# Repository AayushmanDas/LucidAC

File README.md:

# LucidAC: Smart Universal AC Controller & IR Protocol Sniffer

An open-source, handheld, state-machine-driven universal air conditioner remote and IR protocol analyzer built on the ESP32-C3. Designed for multi-vendor AC control with an intuitive rotary UI, live feedback, and a transparent aesthetic enclosure.

---

## Features

- **State-Driven AC Control:** Implements full multi-byte payload serialization across major manufacturers (Daikin, Carrier, Midea, etc.) rather than simple stateless toggles.
- **Physical Rotary Interface:** Smooth navigation and mode scrubbing via an EC11 rotary encoder paired with a 0.96" SSD1306 I2C OLED display.
- **Live IR Learning & Sniffing:** Integrated TSOP1838 receiver enables on-the-fly packet sniffing and timing inspection without an external logic analyzer.
- **Efficient Power Architecture:** 1S LiPo powered with onboard TP4056 USB-C charging (tuned to ~440mA via custom R_PROG), regulated by an ultra-low-dropout ME6211 3.3V LDO.
- **Light Sleep Wake Engine:** Instantaneous sub-millisecond wakeup on encoder movement and push-button interrupts while conserving battery life.
- **Exposed Aesthetic Enclosure:** Custom 3D-printed chassis with a slide-in acrylic window designed to showcase the PCB layout and passives.

---

## Hardware Architecture

| Subsystem | Component | Notes |
| :--- | :--- | :--- |
| **MCU** | ESP32-C3 SuperMini | Socketed via berg headers for safe, isolated flashing |
| **Display** | 0.96" I2C OLED (SSD1306) | Controlled via `U8g2` with power-save sleep toggling |
| **Input** | EC11 Rotary Encoder + Tactile Switch | Interrupt-driven navigation and wake triggers |
| **Optical TX** | 940nm High-Power IR LED | Driven via switching transistor stage |
| **Optical RX** | TSOP1838 (38kHz) | Demodulated carrier sensing for signal reverse-engineering |
| **Power Management** | TP4056 + DW01A / FS8205A | R_PROG = 2.7kΩ (~440mA CC charge rate) |
| **Rail LDO** | ME6211A33M3G (SOT-23-5) | 500mA rating, low dropout, stabilized with 10µF MLCCs |
| **Audio Feedback** | 3.3V Active Buzzer | Short audible confirmation on transmit and menu clicks |

### Decoupling Strategy
The 3.3V power rail uses a multi-tier decoupling scheme:
- **10µF MLCCs:** Fast loop stability directly at the ME6211 input/output pins.
- **100nF Ceramic:** High-frequency RF and digital switching transient suppression near the MCU.
- **100µF Electrolytic:** Bulk reservoir dampening dynamic load steps from the OLED panel and buzzer bursts.

---

## Pinout Mapping

| Function | ESP32-C3 GPIO | Description |
| :--- | :--- | :--- |
| **I2C SDA** | GPIO 8 | OLED Display Data |
| **I2C SCL** | GPIO 9 | OLED Display Clock |
| **Encoder A (CLK)** | GPIO 4 | Interrupt-driven quadrature input |
| **Encoder B (DT)** | GPIO 5 | Quadrature direction sensing |
| **Encoder SW** | GPIO 3 | Primary selection click |
| **Aux Tactile Switch** | GPIO 2 | Secondary trigger / quick action |
| **IR Transmitter** | GPIO 1 | PWM carrier / protocol modulation |
| **IR Receiver** | GPIO 0 | TSOP1838 demodulated input |
| **Buzzer** | GPIO 10 | Active piezo drive |

---

## Firmware Setup

The firmware is developed using **PlatformIO**.

1. Clone this repository:
   ```bash
   git clone [https://github.com/AayushmanDas/LucidAC.git](https://github.com/AayushmanDas/LucidAC.git)
   cd LucidAC/firmware
   ```
2. Open the `firmware/` directory inside VS Code with the PlatformIO extension installed.
3. Build the project:
   ```bash
   pio run
   ```
4. **Flashing Note:** To prevent back-feeding the carrier board's ME6211 regulator, disconnect the SuperMini from its socket headers or power the board normally before plugging in the USB cable.
5. Upload and open the serial monitor:
   ```bash
   pio run -t upload -t monitor
   ```

---

## Mechanical & 3D Printing

- **Enclosure:** Printable without internal supports on standard FDM printers (PLA or PETG, recommended ≥ 4 perimeter walls, 20% infill).
- **Assembly:** Slide the acrylic faceplate into the top guide rails after securing the PCB.

---

## Bill of Materials (BOM)

A complete CSV list of components, footprint packages, and reference designators can be found in [`hardware/BOM.csv`](hardware/BOM.csv).

---

## License

- [MIT License](LICENSE)

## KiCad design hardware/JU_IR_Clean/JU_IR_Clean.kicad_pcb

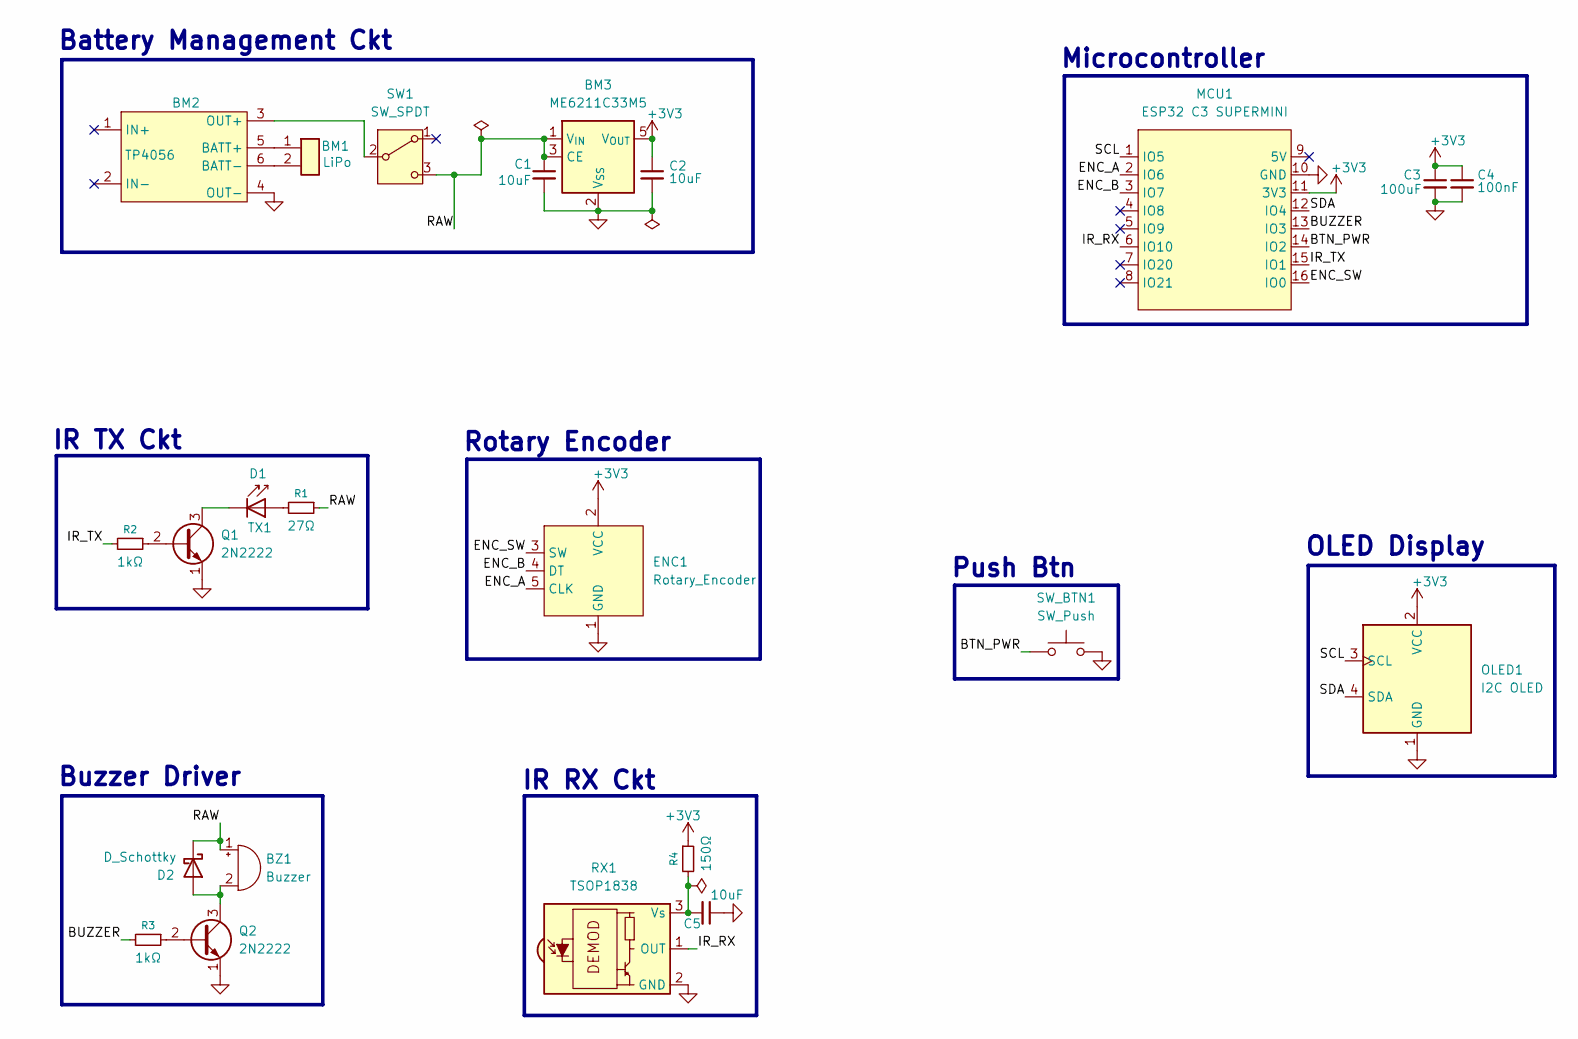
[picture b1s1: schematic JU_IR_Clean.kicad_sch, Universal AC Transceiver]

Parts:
BM1: LiPo; Molex_PicoBlade_53398-0271_1x02-1MP_P1.25mm_Vertical
BM2: TP4056
BM3: ME6211C33M5; SOT-23-5
BZ1: Buzzer; Buzzer_12x9.5RM7.6
C1, C2, C5: 10uF; C_1206_3216Metric_Pad1.33x1.80mm_HandSolder
C3: 100uF; CP_Radial_D6.3mm_P2.50mm
C4: 100nF; C_Disc_D5.0mm_W2.5mm_P2.50mm
D1: TX1; LED_D5.0mm_IRGrey
D2: D_Schottky; D_DO-201AD_P15.24mm_Horizontal
ENC1: Rotary_Encoder; HW-040_Rotary_Encoder
MCU1: ESP32 C3 SUPERMINI; ESP32_C3_SuperMini
OLED1: I2C OLED; OLED_0.96
Q1, Q2: 2N2222; TO-92_Inline
R1: 27Ω; R_Axial_DIN0207_L6.3mm_D2.5mm_P10.16mm_Horizontal
R2, R3: 1kΩ; R_Axial_DIN0207_L6.3mm_D2.5mm_P10.16mm_Horizontal
R4: 150Ω; R_Axial_DIN0207_L6.3mm_D2.5mm_P10.16mm_Horizontal
RX1: TSOP1838; Vishay_MINICAST-3Pin
SW1: SW_SPDT; SolderWire-0.75sqmm_1x03_P4.8mm_D1.25mm_OD2.3mm
SW_BTN1: SW_Push; SW_PUSH_6mm

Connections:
+3V3: BM3.5 (V_{OUT}), C2.1, C3.1, C4.1, ENC1.2 (VCC), MCU1.11 (3V3), OLED1.2 (VCC), R4.1
/BTN_PWR: MCU1.14 (IO2), SW_BTN1.1
/BUZZER: MCU1.13 (IO3), R3.2
/ENC_A: ENC1.5 (CLK), MCU1.2 (IO6)
/ENC_B: ENC1.4 (DT), MCU1.3 (IO7)
/ENC_SW: ENC1.3 (SW), MCU1.16 (IO0)
/IR_RX: MCU1.6 (IO10), RX1.1 (OUT)
/IR_TX: MCU1.15 (IO1), R2.2
/RAW: BM3.1 (V_{IN}), BM3.3 (CE), BZ1.1 (+), C1.1, D2.1 (K), R1.1, SW1.3 (C)
/SCL: MCU1.1 (IO5), OLED1.3 (SCL)
/SDA: MCU1.12 (IO4), OLED1.4 (SDA)
GND: BM2.4 (OUT-), BM3.2 (V_{SS}), C1.2, C2.2, C3.2, C4.2, C5.1, ENC1.1 (GND), MCU1.10 (GND), OLED1.1 (GND), Q1.1 (E), Q2.1 (E), RX1.2 (GND), SW_BTN1.2
unnamed: BM1.1 (+), BM2.5 (BATT+)
unnamed: BM1.2 (-), BM2.6 (BATT-)
unnamed: BM2.3 (OUT+), SW1.2 (B)
unnamed: BZ1.2 (-), D2.2 (A), Q2.3 (C)
unnamed: D1.2 (A), R1.2
unnamed: D1.1 (K), Q1.3 (C)
unnamed: Q1.2 (B), R2.1
unnamed: Q2.2 (B), R3.1
unnamed: C5.2, R4.2, RX1.3 (Vs)

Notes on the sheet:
Battery Management Ckt
Push Btn
OLED Display
Microcontroller
Buzzer Driver
IR RX Ckt
IR TX Ckt
Rotary Encoder

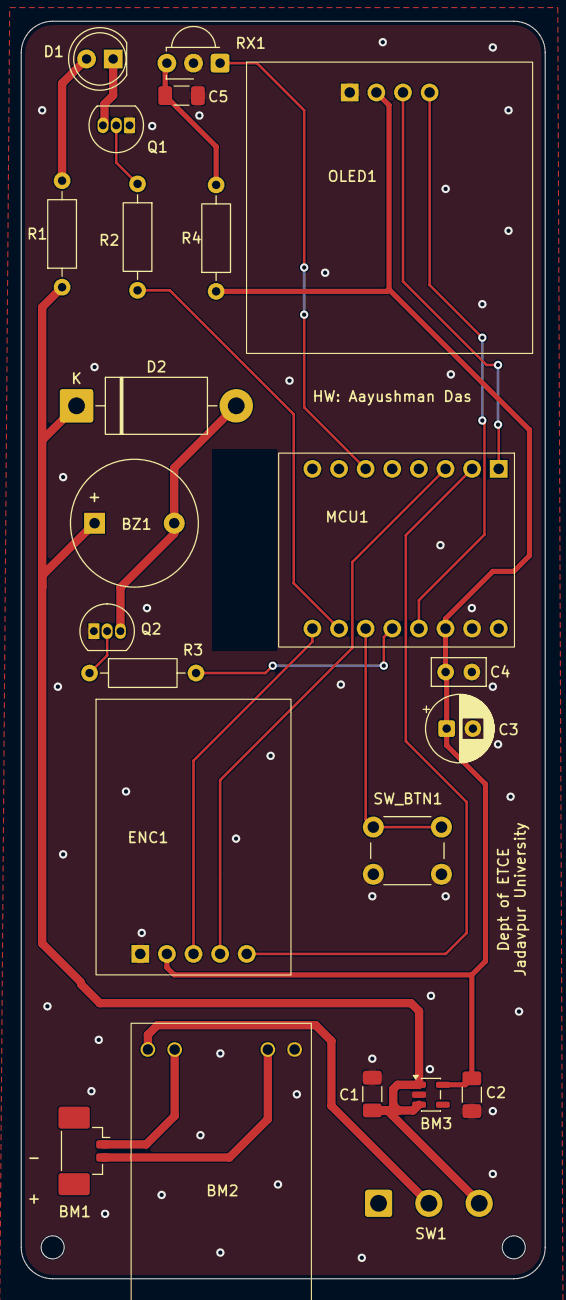
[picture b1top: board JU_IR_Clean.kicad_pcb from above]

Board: 2 copper layers, 50.0 x 120.0 mm, 23 parts (0 on the bottom side), 21 nets.

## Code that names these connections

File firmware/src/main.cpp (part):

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// =================================================================
#define PIN_I2C_SDA     4
#define PIN_I2C_SCL     5
#define PIN_ENC_A       6
#define PIN_ENC_B       7
#define PIN_ENC_SW      0
#define PIN_BTN_PWR     2
#define PIN_BUZZER      3
#define PIN_IR_TX       1
#define PIN_IR_RX       10

// =================================================================
// SYSTEM CONSTANTS & STRUCTURES
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U8G2_SSD1306_128X64_NONAME_F_HW_I2C u8g2(U8G2_R0, U8X8_PIN_NONE);
Preferences prefs;

IRsend irsend(PIN_IR_TX);
IRrecv irrecv(PIN_IR_RX, RAW_BUFFER_CAPACITY, 120, true); // 120 ms gap timeout
decode_results irResults;

// Specific AC Protocol Handlers
IRDaikinESP     irDaikin(PIN_IR_TX);
IRLgAc          irLG(PIN_IR_TX);
IRGreeAC        irVoltas(PIN_IR_TX);   // Voltas via Gree OEM protocol
IRMideaAC       irMidea(PIN_IR_TX);    // Carrier India = Midea OEM (48-bit)
IRHitachiAc     irHitachi(PIN_IR_TX);
IRMitsubishiAC  irMitsubishi(PIN_IR_TX);

// Operational States
AppState currentState = STATE_CONTROL_ROOM;
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// AUDIO FEEDBACK SUBSYSTEM
// =================================================================
void buzzerTrigger(uint16_t durationMs, bool doubleBeep) {
    digitalWrite(PIN_BUZZER, HIGH);
    buzzerStartTime = millis();
    buzzerDuration = durationMs;
    buzzerDoubleBeepPending = doubleBeep;
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    }

    if (buzzerDuration > 0 && (millis() - buzzerStartTime >= buzzerDuration)) {
        digitalWrite(PIN_BUZZER, LOW);
        buzzerDuration = 0;

        if (buzzerDoubleBeepPending) {
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    if (settingsDirty) saveSettings();

    u8g2.setPowerSave(1);
    digitalWrite(PIN_BUZZER, LOW);

    gpio_wakeup_enable((gpio_num_t)PIN_ENC_SW,  GPIO_INTR_LOW_LEVEL);
    gpio_wakeup_enable((gpio_num_t)PIN_BTN_PWR, GPIO_INTR_LOW_LEVEL);
    esp_sleep_enable_gpio_wakeup();

    esp_light_sleep_start();

    esp_sleep_disable_wakeup_source(ESP_SLEEP_WAKEUP_GPIO);
    gpio_wakeup_disable((gpio_num_t)PIN_ENC_SW);
    gpio_wakeup_disable((gpio_num_t)PIN_BTN_PWR);
    u8g2.setPowerSave(0);

    encSwIgnore  = true;
    pwrBtnIgnore = true;

    oldEncoderState = (digitalRead(PIN_ENC_A) << 1) | digitalRead(PIN_ENC_B);
    positionDelta = 0;

    lastActivityTime = millis();
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    Serial.begin(115200);
    delay(500);

    pinMode(PIN_ENC_A,   INPUT_PULLUP);
    pinMode(PIN_ENC_B,   INPUT_PULLUP);
    pinMode(PIN_ENC_SW,  INPUT_PULLUP);
    pinMode(PIN_BTN_PWR, INPUT_PULLUP);
    pinMode(PIN_BUZZER,  OUTPUT);
    digitalWrite(PIN_BUZZER, LOW);

    oldEncoderState = (digitalRead(PIN_ENC_A) << 1) | digitalRead(PIN_ENC_B);

    Wire.begin(PIN_I2C_SDA, PIN_I2C_SCL);
    u8g2.setBusClock(400000);
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    // -------------------------------------------------------------
    // 1. ROTARY ENCODER ROTATION
    // -------------------------------------------------------------
    uint8_t newEncoderState = (digitalRead(PIN_ENC_A) << 1) | digitalRead(PIN_ENC_B);

    if (newEncoderState != oldEncoderState) {
        uint8_t index = (oldEncoderState << 2) | newEncoderState;
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    // -------------------------------------------------------------
    // 2. ENCODER SWITCH (SHORT CLICK VS 2-SECOND LONG PRESS)
    // -------------------------------------------------------------
    int currentEncSw = digitalRead(PIN_ENC_SW);

    if (encSwIgnore) {
        lastActivityTime = millis();
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    } else {
        if (currentEncSw == LOW && !encSwPressed) {
            delay(DEBOUNCE_DELAY_MS);
            if (digitalRead(PIN_ENC_SW) == LOW) {
                encSwPressed = true;
                encSwPressTime = millis();
                lastActivityTime = millis();
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    // -------------------------------------------------------------
    // 3. SIDE POWER BUTTON (BTN_PWR)
    // -------------------------------------------------------------
    int currentPwrBtn = digitalRead(PIN_BTN_PWR);

    if (pwrBtnIgnore) {
        lastActivityTime = millis();
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    } else {
        if (currentPwrBtn == LOW && !pwrBtnPressed) {
            delay(DEBOUNCE_DELAY_MS);
            if (digitalRead(PIN_BTN_PWR) == LOW) {
                pwrBtnPressed = true;
                pwrBtnPressTime = millis();
                lastActivityTime = millis();
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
